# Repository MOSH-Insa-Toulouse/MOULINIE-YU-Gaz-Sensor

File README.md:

# Connected gas sensor / LoRa TTN
Project 5th ISS - MOSH - TP Gas Sensor
Authors: MOULINIÉ Dorian & YU Juan from INSA Toulouse - 5 ISS

# Description

This main goal of this project is to build a connected nanoparticle gas sensor to monitor the concentration of gas.

For this, we used an Arduino UNO and RN2483 LoRa chip to send data on the The Things Network.

We used Kicad for building this shield. Because it is an Open Source Electronics Design Automation Suite. We are able to use  the Schematic Capture and the PCB Layout along with the 3D Viewer in it. They can help us have a more specific view of our shield.

# Content

a KiCad project manage file

KiCad Schematic files

KiCad PCB Files: A shield for the gas sensor and the LoRa Module to plug in an Arduino Uno

KiCad Libraries

Pictures of the components

Readme file

## Overview

This shield is composed of:

 - a LoRa Module (RN2483) as transceiver
 - a Gas sensor
 - an amplifier (LTC1050)
 - a Groove connector for future calibration of the Gas Sensor

First, we created the project with an arduino UNO

Then, we created a library symbol for LTC 1050

Afterwards, we created the following circuit :

### PCB

In order to add the gas sensor to the board, we first created an new footprint. 

After we had all the components prepared, we started to do the routage.

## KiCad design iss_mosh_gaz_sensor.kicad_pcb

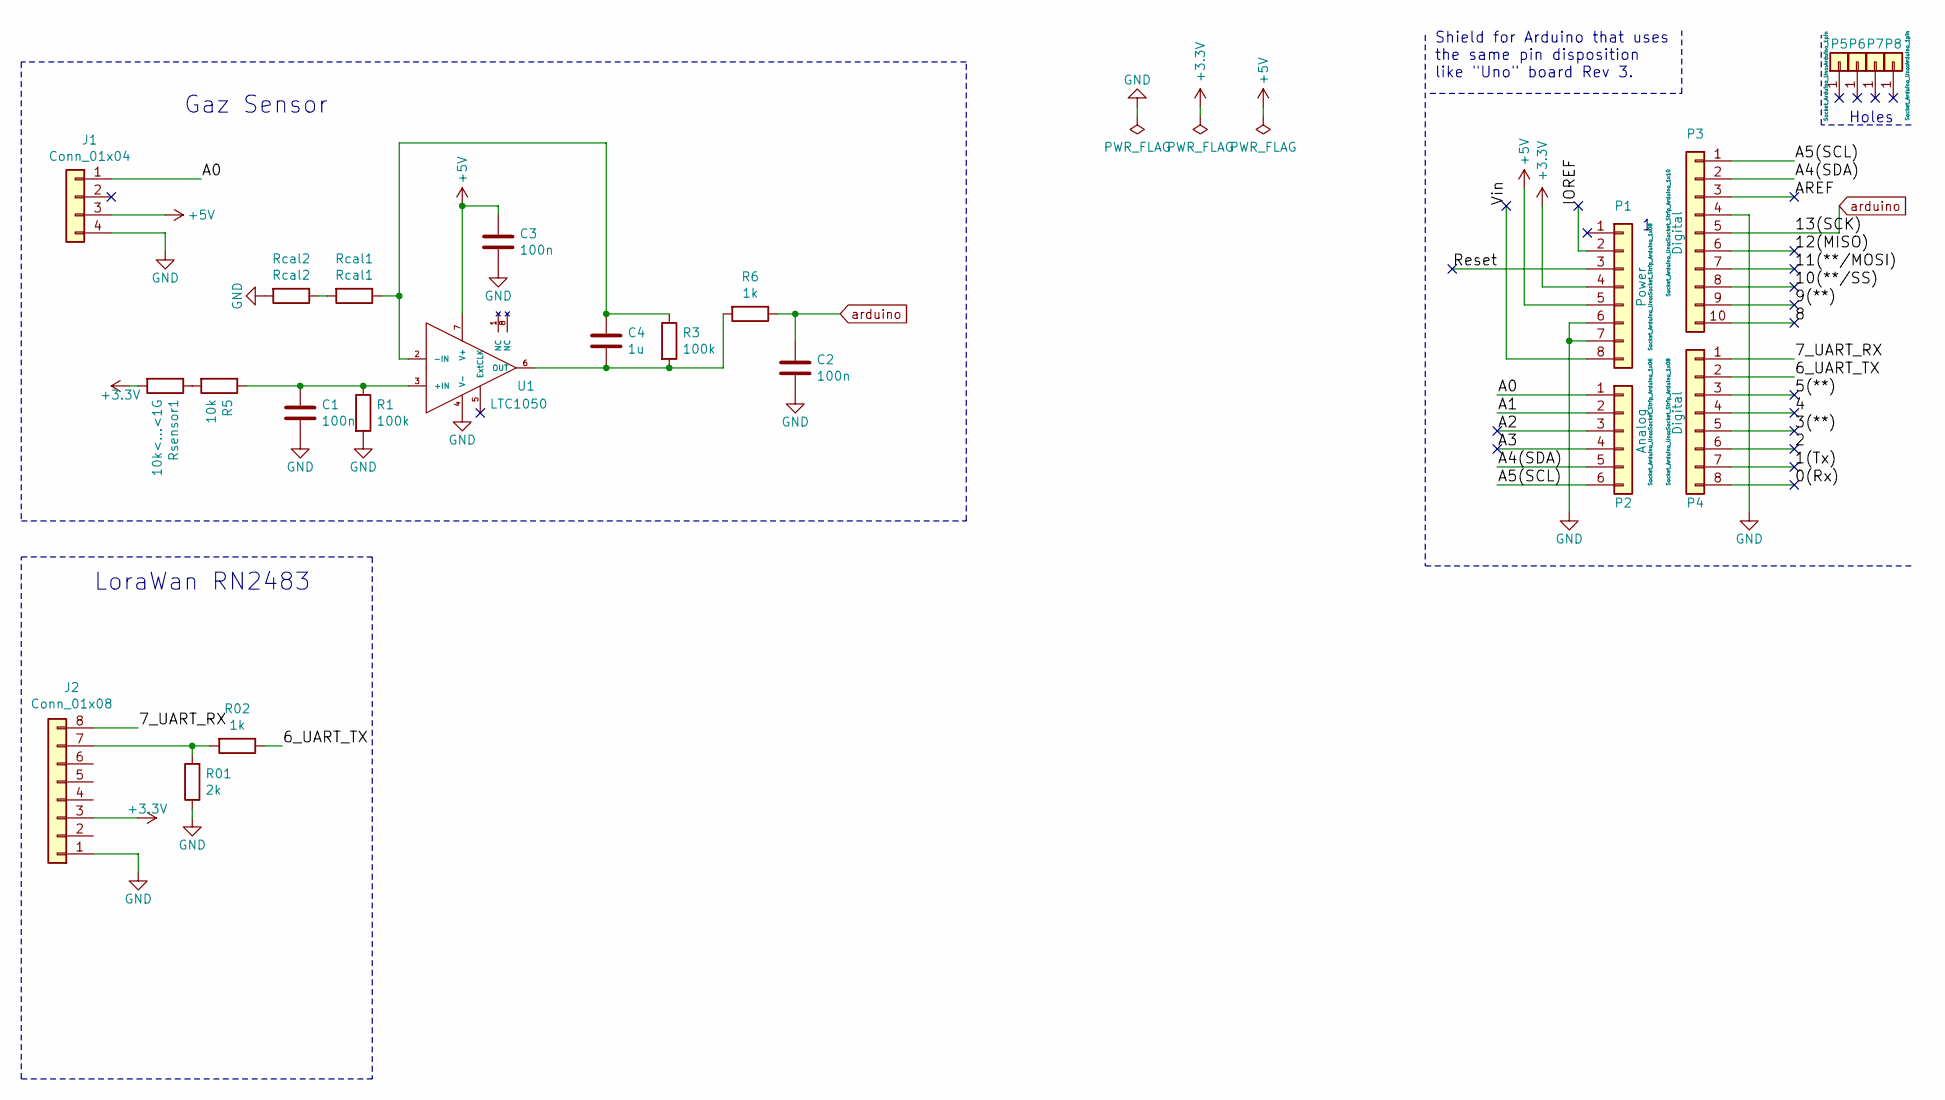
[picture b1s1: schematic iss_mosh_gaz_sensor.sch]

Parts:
C1, C2, C3: 100n; C_Disc_D3.0mm_W1.6mm_P2.50mm
C4: 1u; C_Disc_D3.0mm_W1.6mm_P2.50mm
J1: Conn_01x04; PinSocket_1x04_P2.54mm_Vertical
J2: Conn_01x08; PinSocket_1x08_P2.54mm_Vertical
P1: Power; Socket_Strip_Arduino_1x08
P2: Analog; Socket_Strip_Arduino_1x06
P3: Digital; Socket_Strip_Arduino_1x10
P4: Digital; Socket_Strip_Arduino_1x08
P5, P6, P7, P8: CONN_01X01; Arduino_1pin
R01: 2k; R_Axial_DIN0204_L3.6mm_D1.6mm_P5.08mm_Horizontal
R1, R3: 100k; R_Axial_DIN0204_L3.6mm_D1.6mm_P5.08mm_Horizontal
R02, R6: 1k; R_Axial_DIN0204_L3.6mm_D1.6mm_P5.08mm_Horizontal
R5: 10k; R_Axial_DIN0204_L3.6mm_D1.6mm_P5.08mm_Horizontal
Rcal1: Rcal1; R_Axial_DIN0204_L3.6mm_D1.6mm_P5.08mm_Horizontal
Rcal2: Rcal2; R_Axial_DIN0204_L3.6mm_D1.6mm_P5.08mm_Horizontal
Rsensor1: 10k<...<1G; TO-5-4(gas_sensor)
U1: LTC1050; DIP-8_W7.62mm_LongPads

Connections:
+3V3: J2.3, P1.4, Rsensor1.2
+5V: C3.1, J1.3, P1.5, U1.7 (V+)
/0(Rx): P4.8
/1(Tx): P4.7
/2: P4.6
/3(**): P4.5
/4: P4.4
/5(**): P4.3
/6_UART_TX: P4.2, R02.1
/7_UART_RX: J2.8, P4.1
/8: P3.10
/9(**): P3.9
/10(**/SS): P3.8
/11(**/MOSI): P3.7
/12(MISO): P3.6
/A0: J1.1, P2.1
/A1: P2.2
/A2: P2.3
/A3: P2.4
/A4(SDA): P2.5, P3.2
/A5(SCL): P2.6, P3.1
/AREF: P3.3
/IOREF: P1.2
/Reset: P1.3
/Vin: P1.8
GND: C1.1, C2.2, C3.2, J1.4, J2.1, P1.6, P1.7, P3.4, R01.1, R1.2, Rcal2.2, U1.4 (V-)
unnamed: C1.2, R1.1, R5.1, U1.3 (+IN)
unnamed: C4.1, R3.1, Rcal1.1, U1.2 (-IN)
unnamed: C4.2, R3.2, R6.2, U1.6 (OUT)
unnamed: J2.7, R01.2, R02.2
unnamed: R5.2, Rsensor1.1
unnamed: Rcal1.2, Rcal2.1
arduino: C2.1, P3.5, R6.1

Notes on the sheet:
Holes
Shield for Arduino that uses the same pin disposition like "Uno" board Rev 3.
Gaz Sensor
LoraWan RN2483

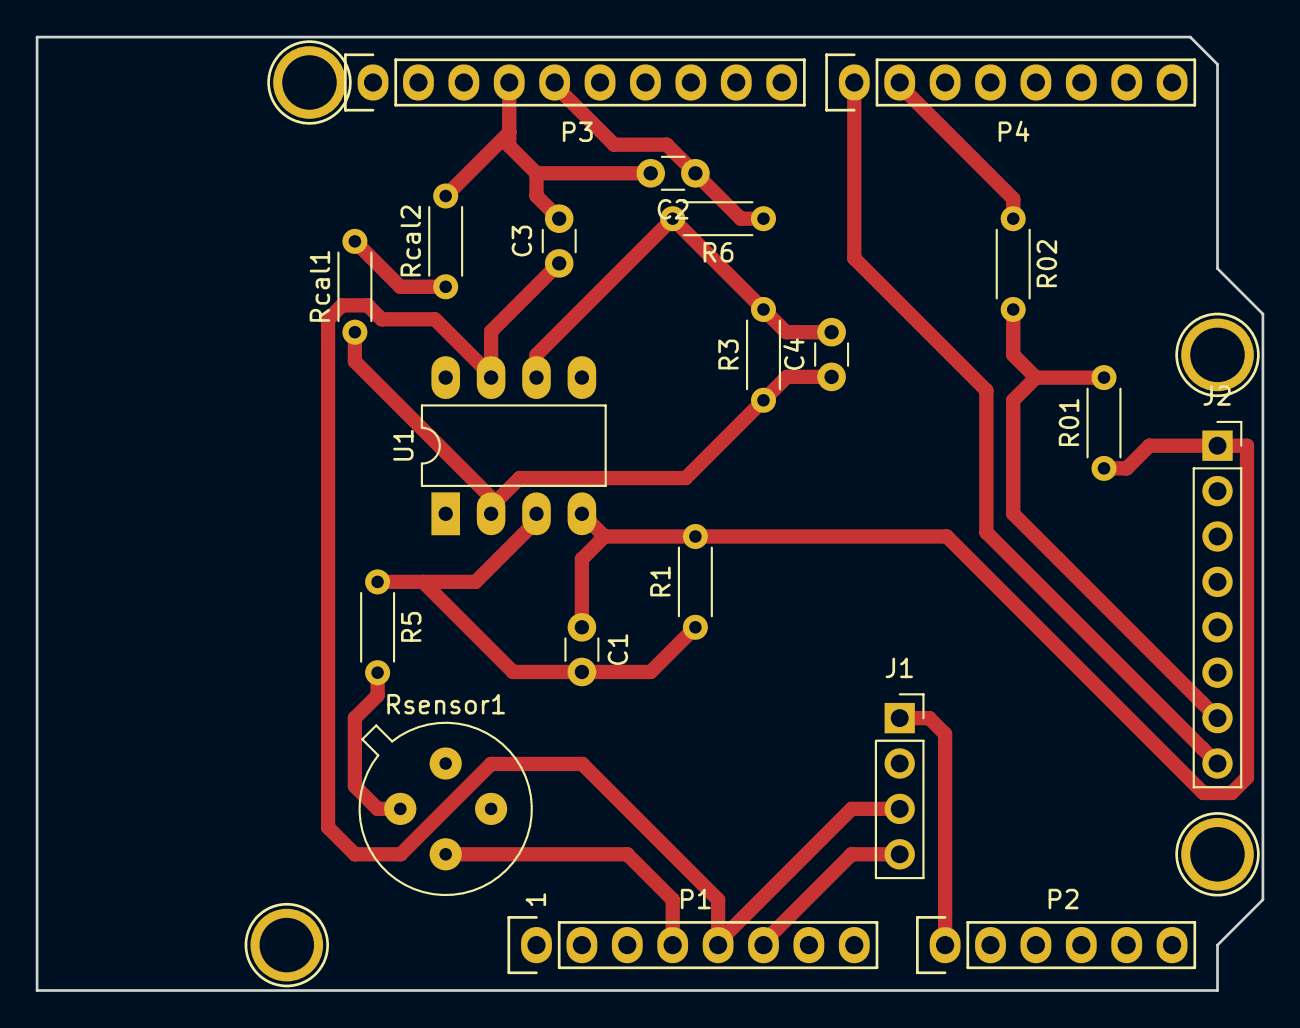
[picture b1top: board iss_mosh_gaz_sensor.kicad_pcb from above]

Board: 2 copper layers, 68.6 x 53.3 mm, 24 parts (0 on the bottom side), 15 nets.

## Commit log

2018-10-31 init
2018-10-31 Add LoraWan RN2483 connectic
2018-11-19 add TO5 gas sensor
2018-11-22 add LTC1050
2018-11-22 gas_sensor_schema
    not all done, half way to success :)
2018-11-22 gaz sensor(not done)
2018-11-22 name change for R1
2018-11-30 Add footprint of components
2018-11-30 Wiring
2018-11-30 Capacitor
2018-11-30 routage
2018-11-30 masse
